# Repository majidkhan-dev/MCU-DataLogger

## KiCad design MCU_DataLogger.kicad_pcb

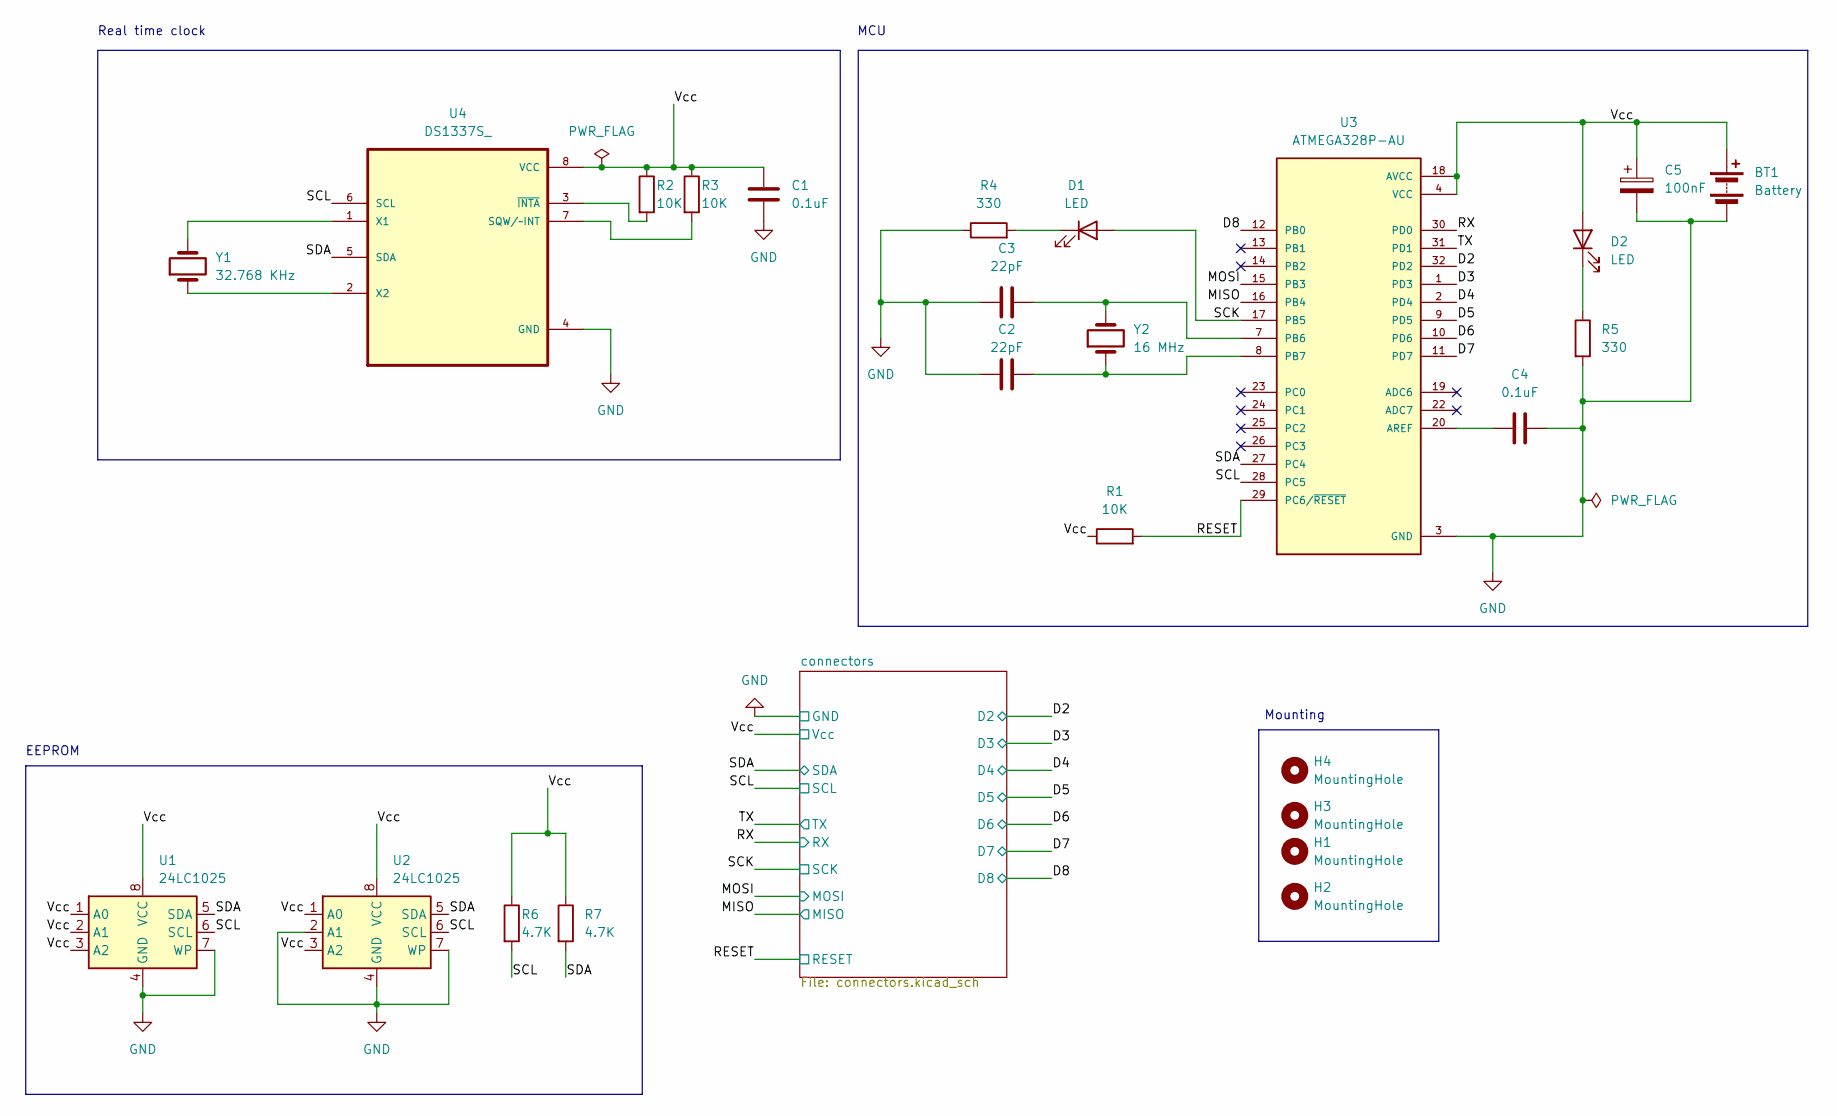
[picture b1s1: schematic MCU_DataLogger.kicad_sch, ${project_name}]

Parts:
BT1: Battery; PinHeader_1x02_P2.54mm_Vertical
C1, C4: 0.1uF; C_0805_2012Metric
C2, C3: 22pF; C_0805_2012Metric
C5: 100nF; C_0805_2012Metric
D1, D2: LED; LED_0805_2012Metric
H1, H2, H3, H4: MountingHole; MountingHole_2.1mm
R1, R2, R3: 10K; R_0805_2012Metric
R4, R5: 330; R_0805_2012Metric
R6, R7: 4.7K; R_0805_2012Metric
U1, U2: 24LC1025; SOIC-8_5.3x5.3mm_P1.27mm
U3: ATMEGA328P-AU; QFP80P900X900X120-32N; PARTREV 8271A
U4: DS1337S_; SOIC127P600X175-8N
Y1: 32.768 KHz; Crystal_SMD_5032-2Pin_5.0x3.2mm_HandSoldering
Y2: 16 MHz; Crystal_SMD_5032-2Pin_5.0x3.2mm_HandSoldering

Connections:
/D2: U3.32 (PD2); also elsewhere on the board
/D3: U3.1 (PD3); also elsewhere on the board
/D4: U3.2 (PD4); also elsewhere on the board
/D5: U3.9 (PD5); also elsewhere on the board
/D6: U3.10 (PD6); also elsewhere on the board
/D7: U3.11 (PD7); also elsewhere on the board
/D8: U3.12 (PB0); also elsewhere on the board
/MISO: U3.16 (PB4); also elsewhere on the board
/MOSI: U3.15 (PB3); also elsewhere on the board
/RESET: R1.2, U3.29 (PC6/~RESET); also elsewhere on the board
/RX: U3.30 (PD0); also elsewhere on the board
/SCK: D1.2 (A), U3.17 (PB5); also elsewhere on the board
/SCL: R6.2, U1.6 (SCL), U2.6 (SCL), U3.28 (PC5), U4.6 (SCL); also elsewhere on the board
/SDA: R7.2, U1.5 (SDA), U2.5 (SDA), U3.27 (PC4), U4.5 (SDA); also elsewhere on the board
/TX: U3.31 (PD1); also elsewhere on the board
GND: BT1.2 (-), C1.2, C2.1, C3.1, C4.2, C5.2, R4.1, R5.2, U1.4 (GND), U1.7 (WP), U2.2 (A1), U2.4 (GND), U2.7 (WP), U3.3 (GND), U3.5 (GND), U3.21 (GND), U4.4 (GND); also elsewhere on the board
unnamed: D1.1 (K), R4.2
unnamed: D2.1 (K), R5.1
unnamed: C4.1, U3.20 (AREF)
unnamed: C3.2, U3.7 (PB6), Y2.2
unnamed: C2.2, U3.8 (PB7), Y2.1
unnamed: R3.2, U4.7 (SQW/~INT)
unnamed: U4.1 (X1), Y1.2
unnamed: U4.2 (X2), Y1.1
unnamed: R2.2, U4.3 (~INTA)
VCC: BT1.1 (+), C1.1, C5.1, D2.2 (A), R1.1, R2.1, R3.1, R6.1, R7.1, U1.1 (A0), U1.2 (A1), U1.3 (A2), U1.8 (VCC), U2.1 (A0), U2.3 (A2), U2.8 (VCC), U3.4 (VCC), U3.6 (VCC), U3.18 (AVCC), U4.8 (VCC); also elsewhere on the board

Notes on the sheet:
Real time clock
EEPROM
Mounting
MCU

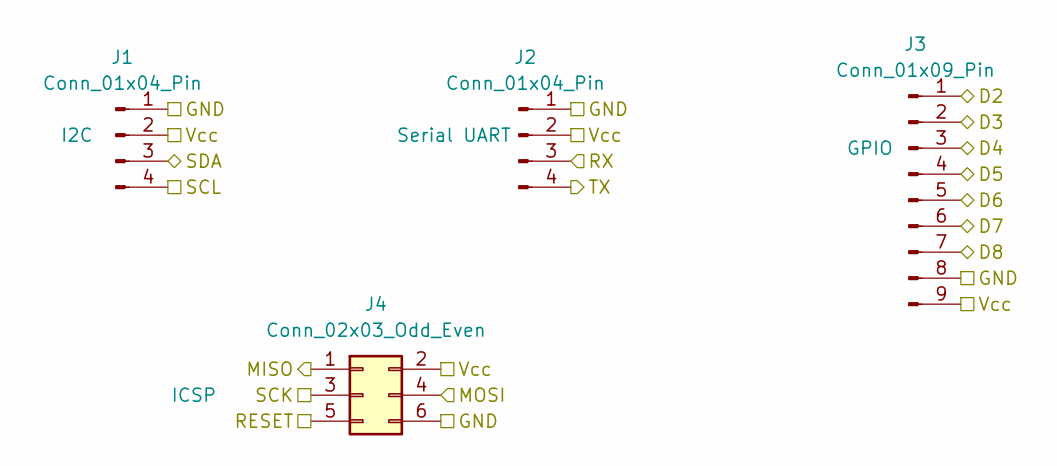
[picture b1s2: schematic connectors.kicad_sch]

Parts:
J1, J2: Conn_01x04_Pin; PinHeader_1x04_P2.54mm_Vertical
J3: Conn_01x09_Pin; PinHeader_1x09_P2.54mm_Vertical
J4: Conn_02x03_Odd_Even; PinHeader_2x03_P2.54mm_Vertical

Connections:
/D2: J3.1; also elsewhere on the board
/D3: J3.2; also elsewhere on the board
/D4: J3.3; also elsewhere on the board
/D5: J3.4; also elsewhere on the board
/D6: J3.5; also elsewhere on the board
/D7: J3.6; also elsewhere on the board
/D8: J3.7; also elsewhere on the board
/MISO: J4.1; also elsewhere on the board
/MOSI: J4.4; also elsewhere on the board
/RESET: J4.5; also elsewhere on the board
/RX: J2.3; also elsewhere on the board
/SCK: J4.3; also elsewhere on the board
/SCL: J1.4; also elsewhere on the board
/SDA: J1.3; also elsewhere on the board
/TX: J2.4; also elsewhere on the board
GND: J1.1, J2.1, J3.8, J4.6; also elsewhere on the board
VCC: J1.2, J2.2, J3.9, J4.2; also elsewhere on the board

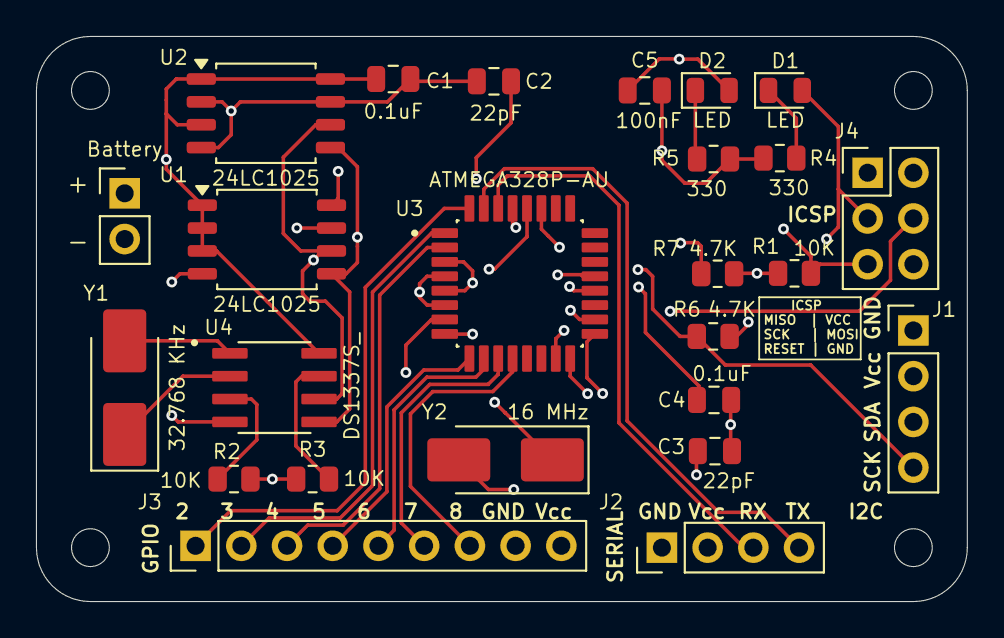
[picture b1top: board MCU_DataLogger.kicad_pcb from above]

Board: 4 copper layers, 51.7 x 31.4 mm, 29 parts (0 on the bottom side), 26 nets.
